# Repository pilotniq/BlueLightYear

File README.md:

# Light Blue Year

A PCB designed in KiCAD for mounting the Core51822 module using the
Nordic Semiconductor nRF51822 BLE microcontroller.

Has footprints for a voltage divider and capacitor for battery voltage
sensing.

Designed for (optional) use with a holder for two AAA batteries, which
should last over a year with low intensity usage.

Footprints for a temperature and air humidity sensor chips on a part of
the board that can be broken off.

Two mounting holes, and a hole to hang the board on.

Since the connectors for the Core51822 use 2 mm pitch, and smt connectors
for it cost more than the nRF module itself, the idea heare is to mount
the Core51822 on the underside of the board, just soldering it. Then 
mount the battery holder on top of it.

All pins from the module are broken out.

A 4 pin SWD programming header is also broken out.

Has a prototyping area.

I2C pull up resistors have footprints on the board. And one LED.

Mount what you want, leave the rest unpopulated.

Intended for manual (not stencil) soldering of the SMT components.

There is a footprint for one SMT LED and one IR Phototransistor.

Also a separate battery connector can be mounted if desired.

Designed in collaboration with @possan

This is my first project with KiCAD, please have oversight with any
strangeness.

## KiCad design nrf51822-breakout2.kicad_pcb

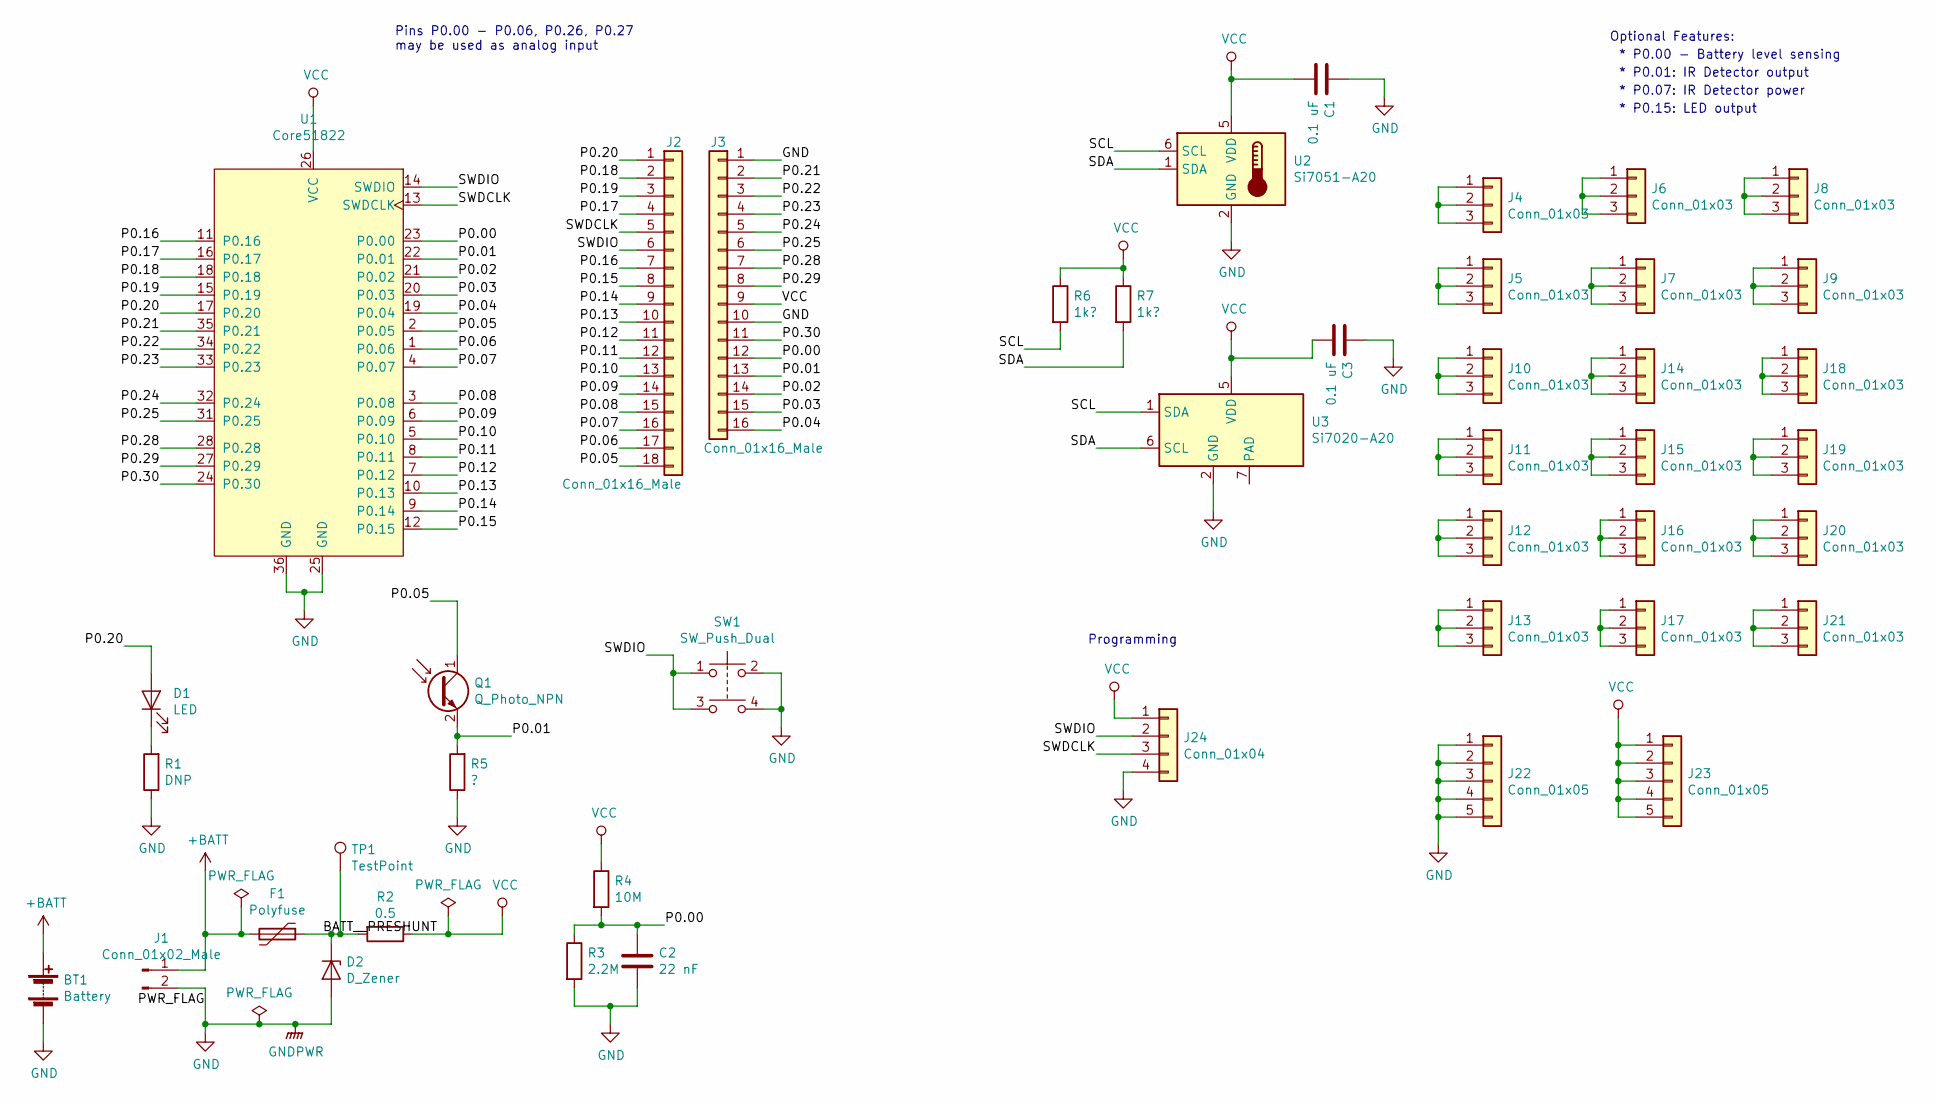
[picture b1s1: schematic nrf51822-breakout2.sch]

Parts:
BT1: Battery; BatteryHolder_Keystone_2468_2xAAA
C1, C3: 0.1 uF; C_0603_HandSoldering
C2: 22 nF; C_0603_HandSoldering
D1: LED; LED_0603_HandSoldering
D2: D_Zener; D_SOD-323
F1: Polyfuse; Fuse_SMD1206_HandSoldering
J1: Conn_01x02_Male; JST_XH_S02B-XH-A_02x2.50mm_Angled
J2: Conn_01x16_Male; Pin_Header_Straight_1x18_Pitch2.54mm
J3: Conn_01x16_Male; Pin_Header_Straight_1x16_Pitch2.54mm
J4, J5, J6, J7, J8, J9, J10, J11, J12, J13, J14, J15, J16, J17, J18, J19, J20, J21: Conn_01x03; tripad
J22, J23: Conn_01x05; Pin_Header_Straight_1x05_Pitch2.54mm
J24: Conn_01x04; Pin_Header_Straight_1x04_Pitch2.54mm
Q1: Q_Photo_NPN; PhotoDiode_SFH205
R1: DNP; R_0603_HandSoldering
R2: 0.5; R_0603_HandSoldering
R3: 2.2M; R_0603_HandSoldering
R4: 10M; R_0603_HandSoldering
R5: ?; R_0603_HandSoldering
R6, R7: 1k?; R_0603_HandSoldering
SW1: SW_Push_Dual; SW_SPST_EVPBF
TP1: TestPoint; Measurement_Point_Round-TH_Big
U1: Core51822
U2: Si7051-A20; DFN-6-1EP_3x3mm_Pitch0.95mm
U3: Si7020-A20; DFN-6-1EP_3x3mm_Pitch0.95mm

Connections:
+BATT: BT1.1 (+), F1.2, J1.1
/BATT__PRESHUNT: D2.1 (K), F1.1, R2.2, TP1.1
/P0.00: C2.1, J3.12, R3.1, R4.2, U1.23 (P0.00)
/P0.01: J3.13, Q1.2 (E), R5.2, U1.22 (P0.01)
/P0.02: J3.14, U1.21 (P0.02)
/P0.03: J3.15, U1.20 (P0.03)
/P0.04: J3.16, U1.19 (P0.04)
/P0.05: J2.18, Q1.1 (C), U1.2 (P0.05)
/P0.06: J2.17, U1.1 (P0.06)
/P0.07: J2.16, U1.4 (P0.07)
/P0.08: J2.15, U1.3 (P0.08)
/P0.09: J2.14, U1.6 (P0.09)
/P0.10: J2.13, U1.5 (P0.10)
/P0.11: J2.12, U1.8 (P0.11)
/P0.12: J2.11, U1.7 (P0.12)
/P0.13: J2.10, U1.10 (P0.13)
/P0.14: J2.9, U1.9 (P0.14)
/P0.15: J2.8, U1.12 (P0.15)
/P0.16: J2.7, U1.11 (P0.16)
/P0.17: J2.4, U1.16 (P0.17)
/P0.18: J2.2, U1.18 (P0.18)
/P0.19: J2.3, U1.15 (P0.19)
/P0.20: D1.2 (A), J2.1, U1.17 (P0.20)
/P0.21: J3.2, U1.35 (P0.21)
/P0.22: J3.3, U1.34 (P0.22)
/P0.23: J3.4, U1.33 (P0.23)
/P0.24: J3.5, U1.32 (P0.24)
/P0.25: J3.6, U1.31 (P0.25)
/P0.28: J3.7, U1.28 (P0.28)
/P0.29: J3.8, U1.27 (P0.29)
/P0.30: J3.11, U1.24 (P0.30)
/SCL: R6.2, U2.6 (SCL), U3.1 (SDA)
/SDA: R7.2, U2.1 (SDA), U3.6 (SCL)
/SWDCLK: J2.5, J24.3, U1.13 (SWDCLK)
/SWDIO: J2.6, J24.2, SW1.1, SW1.3, U1.14 (SWDIO)
GND: BT1.2 (-), C1.1, C2.2, C3.1, D2.2 (A), J1.2, J3.1, J3.10, J22.1, J22.2, J22.3, J22.4, J22.5, J24.4, R1.1, R3.2, R5.1, SW1.2, SW1.4, U1.25 (GND), U1.36 (GND), U2.2 (GND), U3.2 (GND)
unnamed: D1.1 (K), R1.2
unnamed: J4.1, J4.2, J4.3
unnamed: J5.1, J5.2, J5.3
unnamed: J6.1, J6.2, J6.3
unnamed: J7.1, J7.2, J7.3
unnamed: J8.1, J8.2, J8.3
unnamed: J9.1, J9.2, J9.3
unnamed: J10.1, J10.2, J10.3
unnamed: J11.1, J11.2, J11.3
unnamed: J12.1, J12.2, J12.3
unnamed: J13.1, J13.2, J13.3
unnamed: J14.1, J14.2, J14.3
unnamed: J15.1, J15.2, J15.3
unnamed: J16.1, J16.2, J16.3
unnamed: J17.1, J17.2, J17.3
unnamed: J18.1, J18.2, J18.3
unnamed: J19.1, J19.2, J19.3
unnamed: J20.1, J20.2, J20.3
unnamed: J21.1, J21.2, J21.3
VCC: C1.2, C3.2, J3.9, J23.1, J23.2, J23.3, J23.4, J23.5, J24.1, R2.1, R4.1, R6.1, R7.1, U1.26 (VCC), U2.5 (VDD), U3.5 (VDD)

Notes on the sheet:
Pins P0.00 - P0.06, P0.26, P0.27 may be used as analog input
Optional Features:
* P0.00 - Battery level sensing
* P0.01: IR Detector output
* P0.07: IR Detector power
* P0.15: LED output
Programming

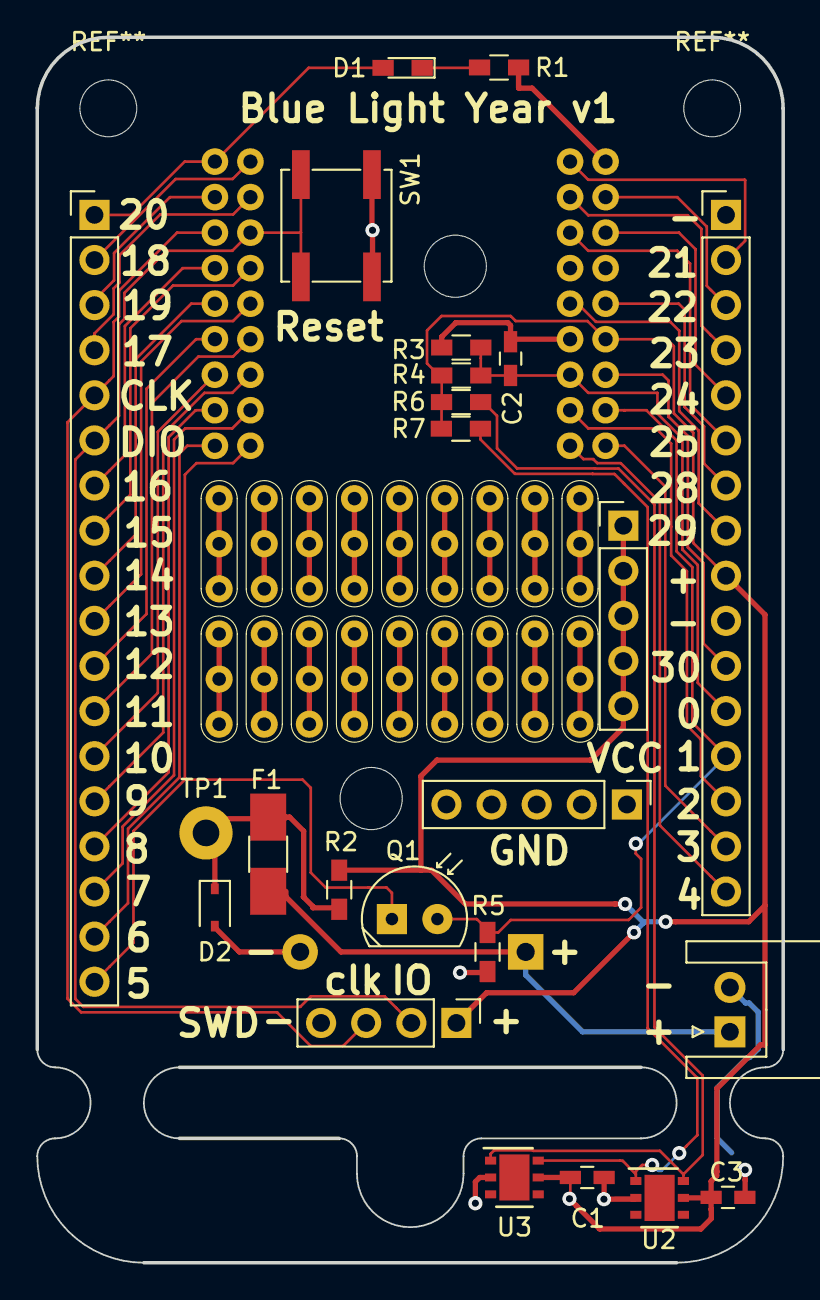
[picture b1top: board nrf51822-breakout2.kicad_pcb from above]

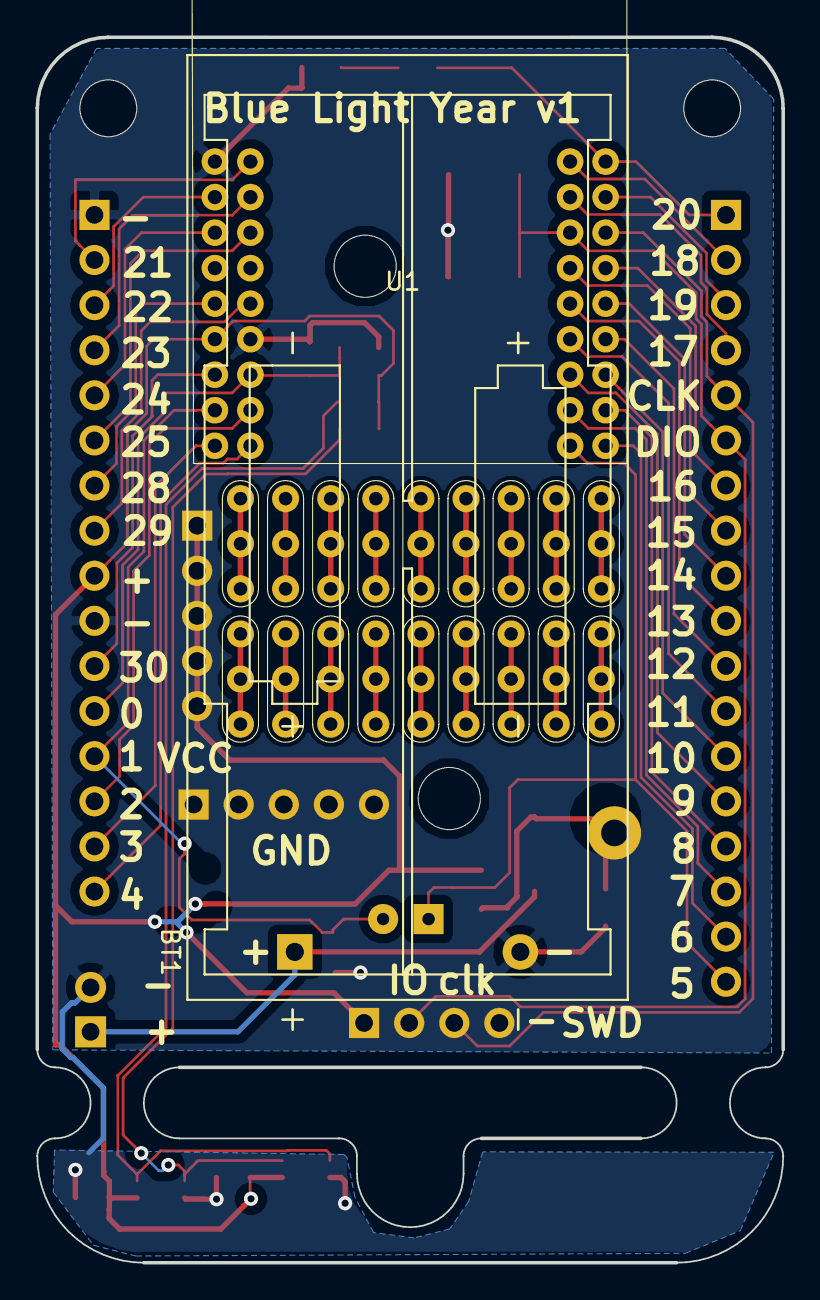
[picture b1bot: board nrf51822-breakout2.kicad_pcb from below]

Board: 2 copper layers, 42.0 x 69.0 mm, 44 parts (2 on the bottom side), 56 nets.

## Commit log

2019-02-13 First version for review
